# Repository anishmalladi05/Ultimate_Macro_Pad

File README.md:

# macropad_xiao

4 x 1 Macro Pad with MX Red Cherry Switches. It will have a metal body. I made this project with QMK firmware and I made it because I frequently switch between my laptop and my laptop plugged into my monitor, where I use a separate keyboard without all of my Mac's shortcuts and stuff, so I wanted a separate, fully customizable solution. I have made it for CNC, but I would like to have a customizable color, and I have a 3D printer, so I think it would be better to 3D print the case for me.

* Keyboard Maintainer: [anishmalladi05](https://github.com/anishmalladi05)
* Hardware Supported: SEEED STUDIO XIAO RP2040
* Hardware Availability: In the BOM

## Bootloader

Enter the bootloader in 3 ways:

* **Physical reset button**: Hold the B button, and while holding, double press the R button, and then release
* **Keycode in layout**: Press the key mapped to `QK_BOOT` if it is available

* Drag the UF2 file into the  microcontroller that you should see appear as a disk after bootloader mode

Picture of product (render):
<br></br>

<br></br>

Routing/Schematic:
<br></br>

<br></br>

PCB:
<br></br>

BOM:
<br></br>
[BILLOFMATERIALS.md](https://github.com/user-attachments/files/28686605/BILLOFMATERIALS.md)
|Name                    |Purpose                                                                                               |Quantity|Total Cost (USD)|Link                                                                                                                                                                                                                                                                                                                                                                                                                                                                                                                                                                                                                                                                                                                                                                       |Distributor|
|------------------------|------------------------------------------------------------------------------------------------------|--------|----------------|---------------------------------------------------------------------------------------------------------------------------------------------------------------------------------------------------------------------------------------------------------------------------------------------------------------------------------------------------------------------------------------------------------------------------------------------------------------------------------------------------------------------------------------------------------------------------------------------------------------------------------------------------------------------------------------------------------------------------------------------------------------------------|-----------|
|Custom Case             |to enclose everything. i will 3d print it so its self funded                                          |1       |84.00           |                                                                                                                                                                                                                                                                                                                                                                                                                                                                                                                                                                                                                                                                                                                                                                           |jlc3dp     |
|Keycaps MX CHERRY RED   |to press but i already have so its self funded                                                        |1       |16.99           |https://www.amazon.com/CHERRY-Silent-Mechanical-Keyboard-Switches/dp/B0FYRGWPGL/ref=sr_1_1_sspa?crid=3AAJ39A48BTCW&dib=eyJ2IjoiMSJ9.mbh2OSxeFi0woU93IJYiWmx03TEHm99NT3zGwuDFDPWqpv6hAgW_8k_iUDWw0WcF2UvreiSerO1g8RbLMeJcHXA6wk8tORoGxKZStaSciLYi_6vmhSC3EUIKwVJ6PsDj1f4V6l3VgVRZyx_b-pUDZa2ZsE7nn23oiAIltiP9jZpQZBK3ah4fohQVN1yzxRXI2R6w9JG8jb2PCvQkuIb2PclF8o44CmqGdqymRSTACks.tqz6PL-ZdX6D4iQJLL3MC5XEHX8ga8Y06im_WF97PV8&dib_tag=se&keywords=mx%2Bcherry%2Bred&qid=1778516185&sprefix=mx%2Bcherry%2Br%2Caps%2C213&sr=8-1-spons&sp_csd=d2lkZ2V0TmFtZT1zcF9hdGY&th=1                                                                                                                                                                                                      |amazon     |
|PCB                     |To connect everything. 3.30 dollar shipping to my address with Global Standard Direct Line (Cheapest))|1       |5.30            |https://cart.jlcpcb.com/shopcart/cart                                                                                                                                                                                                                                                                                                                                                                                                                                                                                                                                                                                                                                                                                                                                      |JLCPCB     |
|Seeed Studio XIAO RP2040|Microcontroller to talk to computer                                                                   |1       |3.99            |https://www.seeedstudio.com/XIAO-RP2040-v1-0-p-5026.html                                                                                                                                                                                                                                                                                                                                                                                                                                                                                                                                                                                                                                                                                                                   |seeedstudio|

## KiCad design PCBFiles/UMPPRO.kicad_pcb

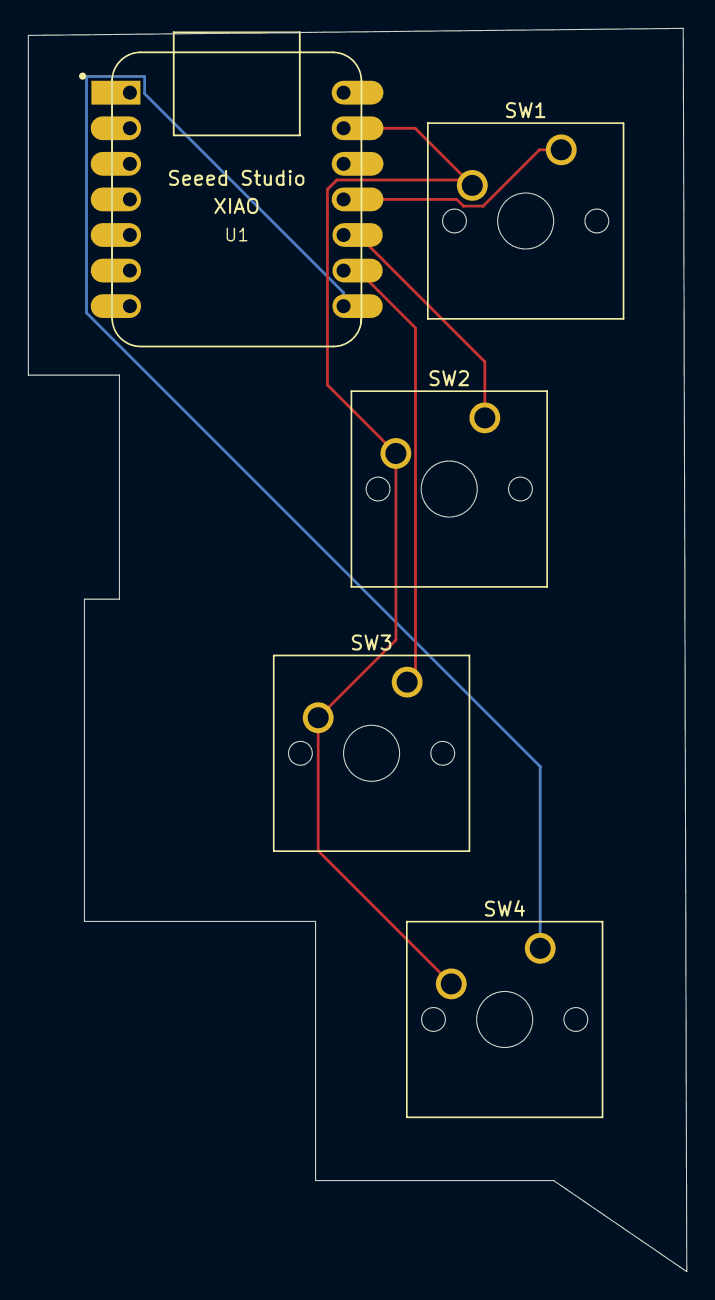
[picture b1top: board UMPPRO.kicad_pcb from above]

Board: 2 copper layers, 47.0 x 88.8 mm, 5 parts (0 on the bottom side), 5 nets.

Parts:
SW1, SW2, SW3, SW4: SW_Push; SW_Cherry_MX_1.00u_PCB
U1: MOUDLE-SEEEDUINO-XIAO; XIAO-Generic-Hybrid-14P-2.54-21X17.8MM

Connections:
GND: SW1.2, SW2.2, SW3.2, SW4.2, U1.13 (GND)
unnamed: SW2.1, U1.10 (PA5_A9_D9_MISO)
unnamed: SW1.1, U1.11 (PA6_A10_D10_MOSI)
unnamed: SW3.1, U1.9 (PA7_A8_D8_SCK)
unnamed: SW4.1, U1.8 (PB09_A7_D7_RX)

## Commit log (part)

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2026-04-08 Initial macropad_xiao QMK firmware
2026-04-08 Add files via upload
    Machine the case parts out of red anodized aluminum.
2026-05-11 Add files via upload
    BOM
2026-05-11 Rename read_me.md to README.md
2026-05-17 Rename 4 x 1 Macro Pad-bom.csv to BILLOFMATERIALS.csv
2026-05-17 Rename ULTIMATE_MACRO_PAD top.step to TOPPART.step
2026-05-17 Rename ULTIMATE_MACRO_PAD bottom.step to BOTTOMPART.step
2026-05-17 Rename BOTTOMPART.step to 3DFiles/BOTTOMPART.step
2026-05-17 Rename CaseBottom.stl to 3DFiles/CaseBottom.stl
2026-05-17 Rename CaseTop.stl to 3DFiles/CaseTop.stl
2026-05-17 Rename TOPPART.step to 3DFiles/TOPPART.step
2026-05-17 Rename GerberFiles.zip to PCBFiles/GerberFiles.zip
2026-05-17 Rename ULTIMATE MACRO PAD.kicad_sch to PCBFiles/ULTIMATE MACRO PAD.kicad_sch
2026-05-17 Rename ULTIMATE MACRO PAD.kicad_pcb to PCBFiles/ULTIMATE MACRO PAD.kicad_pcb
2026-05-17 Rename config.h to keymaps/default/config.h
2026-05-17 Rename keyboard.json to keymaps/default/keyboard.json
2026-05-17 Rename rules.mk to keymaps/default/rules.mk
2026-06-07 Rename UMP.kicad_pro to PCBFiles/UMP.kicad_pro
2026-06-15 Rename 4 x 1 Macro Pad-bom (1).csv to 4 x 1 Macro Pad.csv
